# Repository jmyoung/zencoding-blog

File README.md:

# zencoding-blog
Automatically exported from code.google.com/p/zencoding-blog

This content is ancient, not updated, and mostly here for archival purposes.

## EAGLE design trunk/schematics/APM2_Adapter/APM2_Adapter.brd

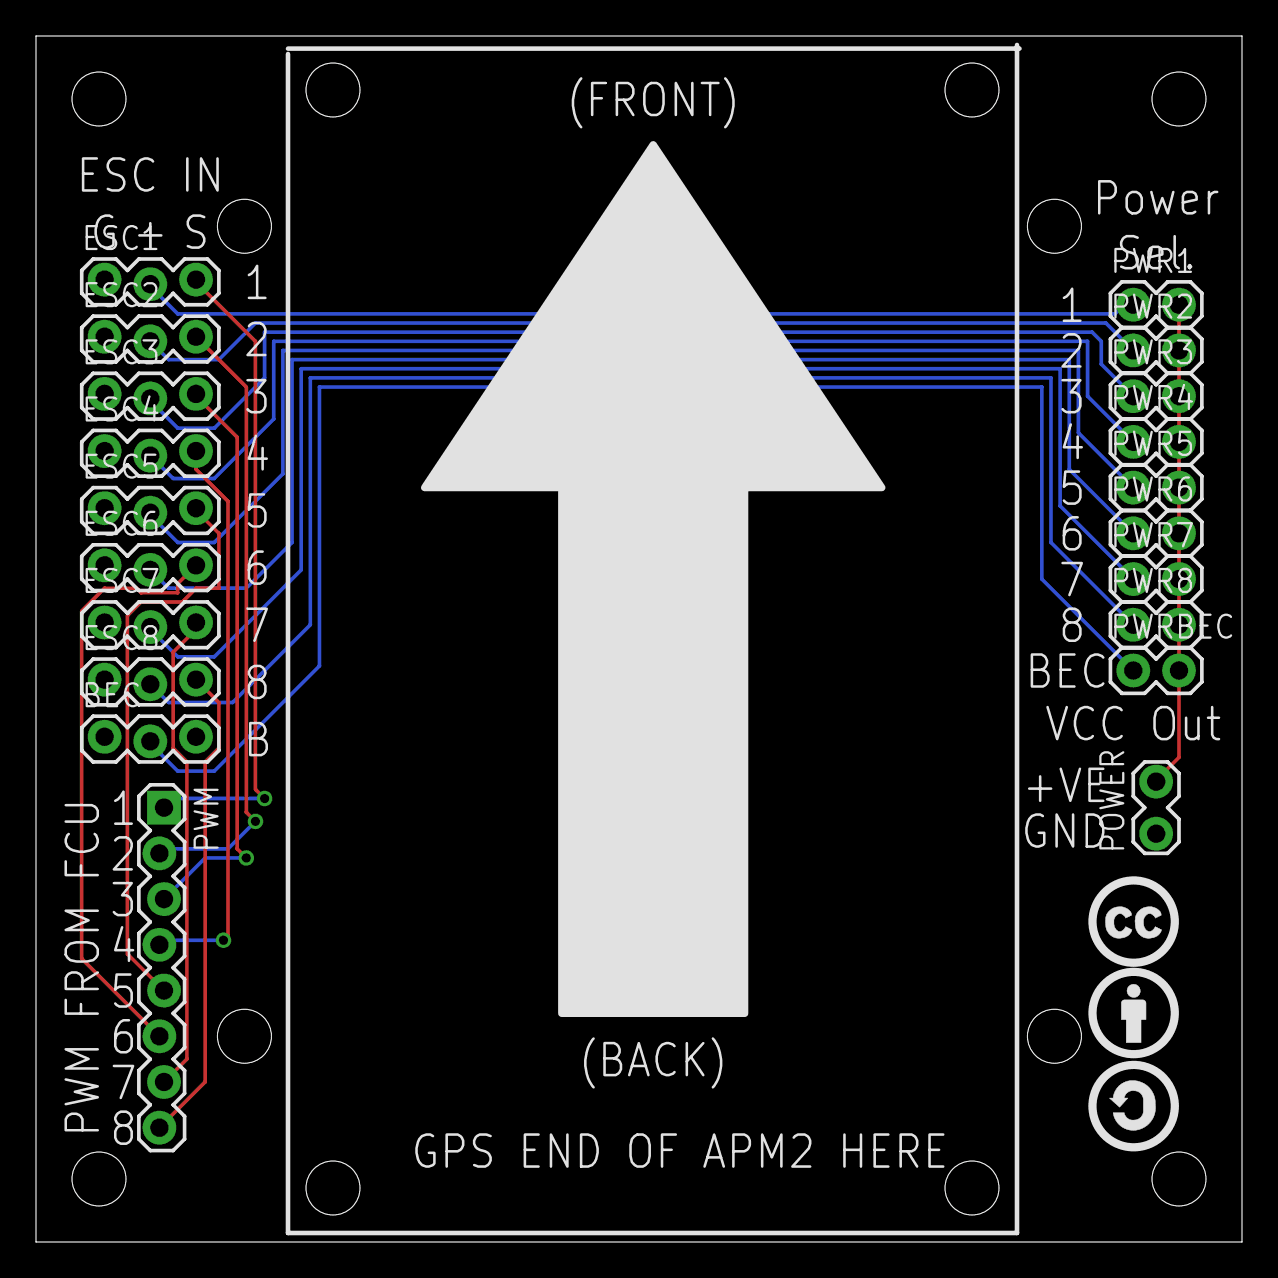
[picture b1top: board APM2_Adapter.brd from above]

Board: 2 copper layers, 67.0 x 67.0 mm, 23 parts (0 on the bottom side), 19 nets.

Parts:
BEC: 1X03_LOCK
ESC1, ESC2, ESC3, ESC4, ESC5, ESC6, ESC7, ESC8: 1X03_LOCK
POWER: 1X02_LOCK
PWM: 1X08_LOCK
PWR1, PWR2, PWR3, PWR4, PWR5, PWR6, PWR7, PWR8: 1X02
PWRBEC: 1X02
U$1: CC
U$2: BY
U$3: SA

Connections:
GND: BEC.1, ESC1.1, ESC2.1, ESC3.1, ESC4.1, ESC5.1, ESC6.1, ESC7.1, ESC8.1, POWER.1
unnamed: ESC1.3, PWM.1
unnamed: ESC2.3, PWM.2
unnamed: ESC3.3, PWM.3
unnamed: ESC4.3, PWM.4
unnamed: ESC5.3, PWM.5
unnamed: ESC6.3, PWM.6
unnamed: ESC7.3, PWM.7
unnamed: ESC8.3, PWM.8
unnamed: ESC2.2, PWR2.1
unnamed: ESC1.2, PWR1.1
unnamed: ESC3.2, PWR3.1
unnamed: ESC4.2, PWR4.1
unnamed: ESC5.2, PWR5.1
unnamed: ESC6.2, PWR6.1
unnamed: ESC7.2, PWR7.1
unnamed: ESC8.2, PWR8.1
unnamed: BEC.2, PWRBEC.1
VCC: POWER.2, PWR1.2, PWR2.2, PWR3.2, PWR4.2, PWR5.2, PWR6.2, PWR7.2, PWR8.2, PWRBEC.2

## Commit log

2011-05-03 Initial directory structure.
2011-05-04 Initial commit of ENVI-R and Arduino files
2011-05-21 Updated design
2011-05-24 Added in plate template
2011-05-25 Updated design and templates
2011-05-25 Extended arm length to 200mm for checking, may reduce to 180mm again
2011-05-26 Constructed template for baseplate and arms
2011-05-26 Added center mark on baseplate (for cable entrance etc)
2011-05-26 Updated baseplate to be 145mm to suit 295mm purchased plate material
2011-05-28 Updated motor template to have bend mark for legs
2011-05-29 Added in landing skid design
2011-06-03 Added schematics for MPC IR Blaster
2011-06-13 Added
2011-07-02 Added Arduinoven boards, schematics, and the Toner Transfer CAM processor
2011-07-05 Updated breakout boards
2011-07-05 Removed invalid transfer
2011-07-13 First commit of _really_ pre-alpha code
2011-07-13 Updated to 1.0RC3
2011-07-13 Implemented PID for first time
2011-07-20 Release version 1.0
2011-08-01 Added BusPirate compatible AVRDUDE binary
2011-08-02 Updated with applied patch
2011-09-07 Updated Arduinoven code extensively
2011-10-11 Fixed up averaging code and parser to support multiple transmitters
2012-03-05 Updated to work with release version 5.11
2012-04-18 Updated BusPirate patches
2012-04-18 Fixed some newline issues
2012-08-06 Initial commit of original files
2012-08-06 Initial commit of original files (moved)
2012-08-06 Removed (moved)
2012-08-06 Correcting busted folders
2012-08-06 Initial Commit of original files (take 2)
2012-08-10 Changes reverted
2012-10-17 Updated Versions for Triplehead
2012-12-04 Added password generator scripts
2012-12-05 Updated the URL
2012-12-06 Changed how the onclick works
2012-12-06 Updated onclick AGAIN
2013-01-14 Incorporated verbosity and progress bar fixes from Nils Steinger.
2013-01-14 Fixed paged_load function to have the correct prototype to remove all warnings
2013-05-04 Removed
2013-05-05 Fix for Ka-50
2013-06-17 Recompiled from latest source
2016-04-14 Migrating wiki contents from Google Code
2016-05-03 Rewrote to use multiple MQTT channels
2016-05-04 Tightened some logic
2016-08-04 Added direct post to Logstash
2017-01-12 Typo
2017-12-22 Reorganized things
2017-12-27 Updated settings

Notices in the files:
trunk/schematics/APM2_Adapter/APM2_Adapter.brd:
Licensed under Creative Commons
parts and their libraries:
SparkFun: Licensing: CC v3.0 Share-Alike You are welcome to use this library for commercial purposes.
